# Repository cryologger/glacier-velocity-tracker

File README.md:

# Cryologger - Glacier Velocity Tracker (GVT)
### Note: This documentation is currently under development.

## 1.0 Introduction

Reliance on expensive and proprietary commercial data acquisition and telemetry systems can present a barrier to monitoring remote polar environments. The development of low-cost, open-source instrumentation can greatly reduce the cost of research in remote locations, improve the spatiotemporal resolution of collected data, and provide new ways to observe and monitor the cryosphere. 

The [Cryologger Glacier Velocity Tracker (GVT)](https://github.com/cryologger/glacier-velocity-tracker) is a novel [Cryologger](https://github.com/cryologger) design configuration intended to collect high temporal resolution velocity measurements to assess glacier dynamics on daily timescales in the Canadian Arctic. The system is based on the Arduino electronics platform and harnesses the u-blox ZED-F9P multi-frequency Global Navigation Satellite System (GNSS) receiver.

## 2.0 Methods

### 2.1 Design
The Cryologger GVT is based on the open-source Arduino platform (www.arduino.cc). Code is written using the Arduino Integrated Development Environment (IDE) and benefits from the availability of community-generated libraries.

The design of the Cryologger GVT takes into consideration several key principles, including cost-effectiveness, power efficiency, modularity, ruggedness, and ease of use. It is comprised of off-the-shelf components that do not require specialized tools or training, making it accessible to researchers, citizen scientists, and hobbyists alike. These selected components are also resistant to harsh environmental conditions, ensuring year-round continuous cold-weather operation.

#### 2.1.1 Bill of materials

The Cryologger GVT is built using almost exclusively using components from [SparkFun](https://www.sparkfun.com/), with a list of the main components shown below. For a more detailed bill of materials, including requirements for power and mounting of a complete deployable system, please see [ASSEMBLY.md](/Documentation/ASSEMBLY.md).

**Table 1.** Main components making up Cryologger GVT. Prices are listed in USD and are current as of December 2023. Taxes and shipping are not included.
| Component | Product | Quantity | Cost (USD) |
| --- | --- | :---: | :---: |
| PCB | [Custom Cryologger Printed Circuit Board](https://jlcpcb.com) | 1 | $5.00 | 
| Processor | [SparkFun MicroMod Artemis Processor](https://www.sparkfun.com/products/16401) | 1 | $14.95 | 
| Carrier Board | [SparkFun MicroMod Data Logging Carrier Board](https://www.sparkfun.com/products/16829) | 1 | $21.50 | 
| GNSS Receiver | [SparkFun GPS-RTK-SMA Breakout - ZED-F9P](https://www.sparkfun.com/products/16481) | 1 | $274.95 | 
| GNSS Antenna | [SparkFun GNSS Multi-Band L1/L2 Surveying Antenna (TNC) - TOP106](https://www.sparkfun.com/products/17751) | 1 | $133.95 | 
| Display | [SparkFun Qwiic OLED Display](https://www.sparkfun.com/products/17153) | 1 | $10.95 |
| Voltage Regulator | [Pololu 5V, 600mA Step-Down Voltage Regulator D36V6F5](https://www.pololu.com/product/3792) | 1 | $6.95 |

#### 2.1.2 Design Evolution 

A carrier board was designed to simplify assembly and deployment. It provides 5.08 mm, 2-pin screw terminals for wiring the battery connection, and a resistor divider to measure battery voltage.

<p align="center"><b>Figure 1.</b> Open-source carrier board design.</p>

#### 2.1.3 Mock-up
The Cryologger GVT was originally intended to be installed in a small electronics enclosure that is mounted in a larger enclosure for deployment outdoors.

<p align="center"><b>Figure 2.</b> Open-source carrier board design.</p>

### 2.2 Operation

When initially powered on, the Cryologger GVT will attempt to establish a GNSS fix and synchronize the real-time clock (RTC) of the MicroMod Artemis Processor for up to 5 minutes. Once the RTC is synchronized, the system will set an alarm to wake at the user-specified time and then enter a low-power deep sleep.  Nominally, the system will wake daily and log data from the u-blox GNSS receiver to a microSD card for a period of 3 hours. There are three different logging modes available to the end end-user, which can be tailored to the data collection requirements and available power capacity.

Versions 2.2.1 and above of the Cryologger GVT are equipped with an OLED display. This display is used to provide detailed information to the end user about the status of the Cryologger at each stage of operation, including boot-up, initialization of components, acquisition of GNSS fix, and logging of data. 

In addition to the OLED display messages, a series of LED blink patterns can also be used to indicate system operation and guide possible troubleshooting steps that should be attempted if any errors is encountered. A detailed table of the LED blink patterns can be found in the [DEPLOYMENT.md](/Documentation/DEPLOYMET.md) documentation. 

While the system is in deep sleep, a Watchdog Timer (WDT) will wake the system to check the program has not frozen every 10 seconds and perform a reset, if necessary. This helps to ensure the long-term reliability of the system.

### 2.3 Data Processing

Data is logged in u-blox's proprietary .ubx format. Log files can be converted to RINEX using RTKLIB or Emlid Studio and submitted to NRCan's Precise Point Positioning (PPP) tool: https://webapp.geod.nrcan.gc.ca/geod/tools-outils/ppp.php

For a more detailed guide on the processing of data, please see "[PROCESSING.md](/Documentation/PROCESSING.md).

## 3.0 Deployments

Between 2021 and 2023, a total of 28 Cryologger GVT deployments were made by several different academic institutions, including the Univerity of Ottawa, Carleton University, University of Waterloo (Canada), Carnegie Mellon University (United States), and University of Fribourg (Switzerland). These deployments were made on glaciers in several geographically distinct locations, including Canada, the United States and Kyrgyzstan. Two case studies of deployments made by the University of Ottawa and the University of Waterloo on glaciers in the Yukon and Nunvaut, Canada are explored in more detail below.

<p align="left"><b>Figure 3.</b> Map of Cryologger GVT deployments made between 2021 and 2023.</p>

### 3.1 Lowell Glacier, Yukon, Canada

<p align="left"><b>Figure 4.</b> Map of Cryologger GVT deployments made in 2021 on the Lowell Glacier, Yukon.</p>

### 3.2 Belcher Glacier, Devon Island, Nunavut, Canada

<p align="left"><b>Figure 5.</b> Map of Cryologger GVT deployments made in 2021 on the Lowell Glacier, Yukon and Belcher Glacier, Devon Island, Nunavut.</p>

<p align="center">&nbsp;&nbsp;</p>
<p align="left"><b>Figure 6.</b> Deployment of the "Belcher Lower" Cryologger GVT on the Belcher Glacier, Devon Island, Nunavut.</p>

## 4.0 Results

Preliminary results from the 2021 deployments of Cryologger GVTs on Lowell Glacier, Kluane National Park, Yukon and Belcher Glacier, Devon Island, Nunavut are presented below.

### 4.1 Lowell Glacier, Yukon, Canada

The initial Cryologger GVTs deployments on Lowell Glacier were both successful, achieving continuous operation throughout the year. 

Collected data that was PPP-processed revealed the GVTs deployed on Lowell Glacier were able to achieve daily position measurements with accuracies of <3 cm. Daily displacements ranged between 0.25 – 4.4 m d<sup>-1</sup> and annual cumulative distances were between 200 – 700 m y<sup>-1</sup>. Both systems showed evidence of ongoing glacier surge cycles and excitingly were also able to capture periods of marked glacier velocity corresponding to local rainfall events and enhanced basal sliding.

<p align="left"><b>Figure 7.</b> Cumulative distance and daily displacement of Lowell Glacier, Yukon recorded between between 2021 and 2022.</p>

### 4.2 Belcher Glacier, Devon Island, Nunavut, Canada

Cryologger GVT deployments made on Belcher Glacier were also able to achieve successful operation throughout the entire year. The data collected between 2021-2022 represents the first uninterrupted annual velocity record of the Belcher Glacier ever recorded.

PPP-processed data showed the GVTs deployed on Belcher Glacier were also able to achieve daily position measurements with accuracies of <3 cm. Daily displacements ranged between 0.18 – 0.45 m d<sup>-1</sup> and annual cumulative distances were between 75 – 150 m y<sup>-1</sup>. These results are also in agreement with velocities derived from synthetic-aperture radar (SAR) remote sensing data.

<p align="left"><b>Figure 8.</b> Cumulative distance and daily displacement of Belcher Glacier, Devon Island recorded between between 2021 and 2022.</p>

## 5.0 Conclusions

Cryologger GVT deployments have demonstrated they can achieve continuous year-round operation. Data processed with Precise Point Positioning techniques also reveals the systems can achieve daily position measurements with accuracies of <3 cm. These promising results demonstrate that open-source hardware and software can provide a reliable and cost-effective alternative to commercially available equipment for use in glaciological monitoring.

## Acknowledgements

This project would not have been possible without the designs, software and tutorials provided by the open-source community. A special thanks to the authors of and contributors to the [SparkFun u-blox GNSS Arduino Library](https://github.com/sparkfun/SparkFun_u-blox_GNSS_Arduino_Library).

## Repository Contents

* **/Documentation** - Assembly, deployment and troubleshooting guides, as well as information on components used and associated costs.

* **/Hardware** - KiCad PCB schematic and design files.

* **/Software** -  Arduino code and Python data analysis scripts.

## License Information
Cryologger code, firmware, and software is licensed under the GNU General Public License v3.0 (https://www.gnu.org/licenses/gpl-3.0.en.html). 

<p xmlns:cc="http://creativecommons.org/ns#" >Cryologger hardware is licensed under <a href="https://creativecommons.org/licenses/by-nc-sa/4.0/?ref=chooser-v1" target="_blank" rel="license noopener noreferrer" style="display:inline-block;">CC BY-NC-SA 4.0 </a></p>

Cheers,

**Adam Garbo**

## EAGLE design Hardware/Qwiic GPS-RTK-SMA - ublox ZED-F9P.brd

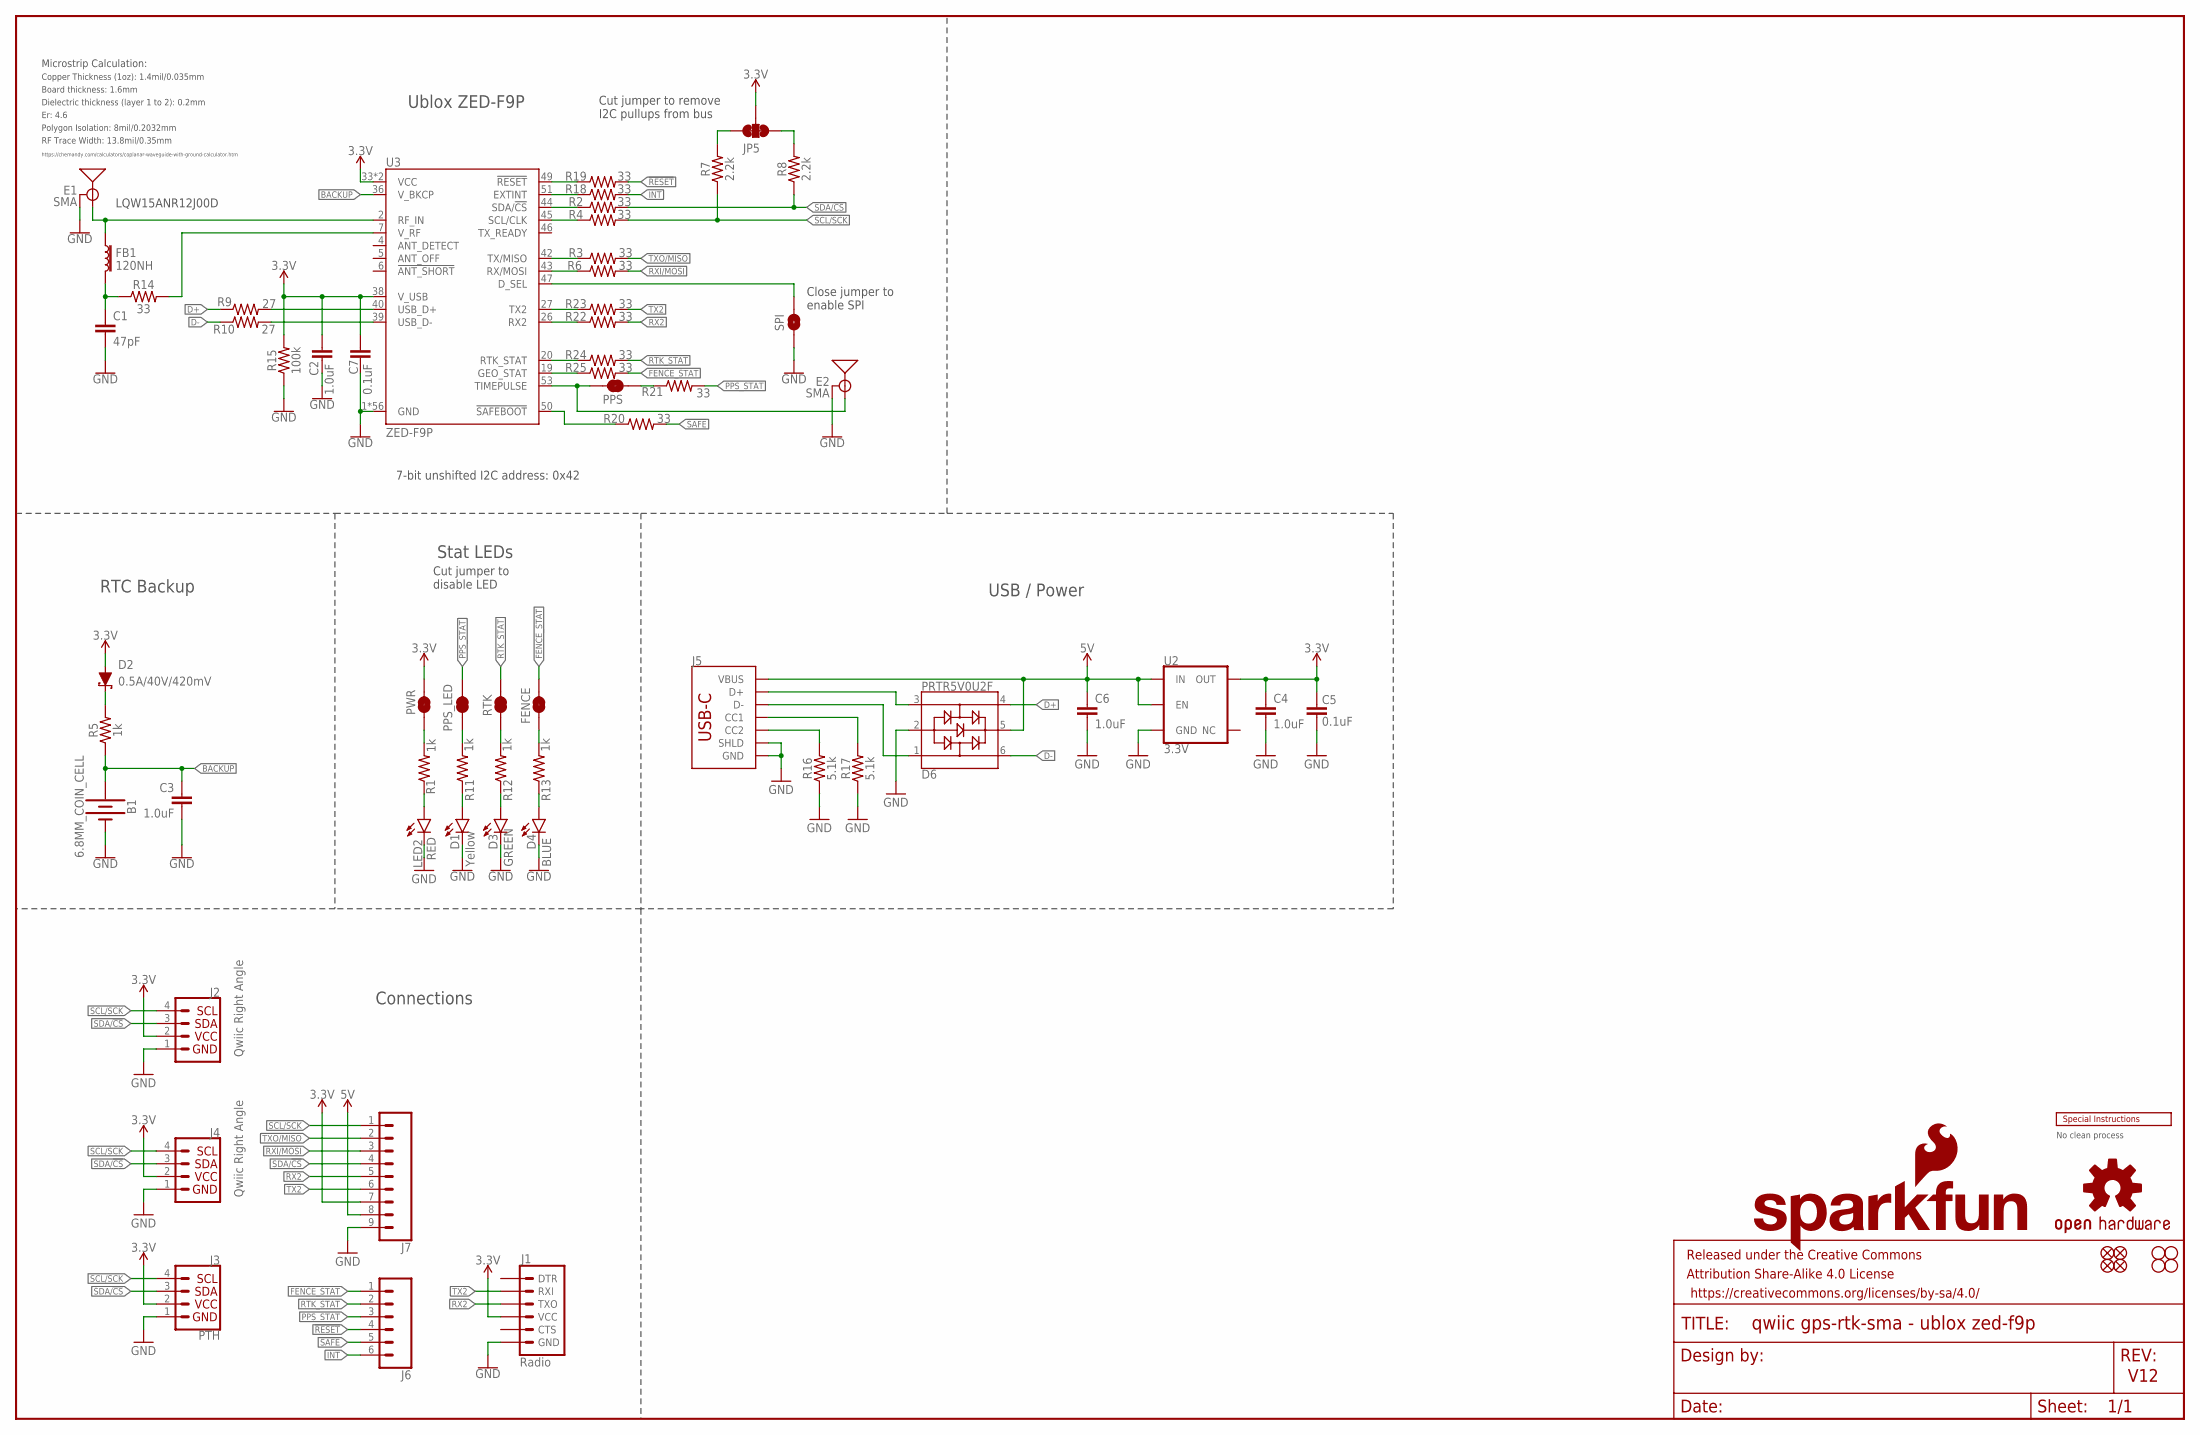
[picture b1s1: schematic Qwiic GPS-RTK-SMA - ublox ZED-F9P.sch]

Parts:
B1: 6.8MM_COIN_CELL; ML414H_IV01E
C1: 47pF; 0402
C2, C3, C4, C6: 1.0uF; 0603
C5, C7: 0.1uF; 0603
D1: Yellow; LED-0603
D2: 0.5A/40V/420mV; SOD-323
D3: GREEN; LED-0603
D4: BLUE; LED-0603
D6: PRTR5V0U2F; SOT886
E1, E2: SMA; SMA-EDGE
FB1: 120NH; 0402_MURATA
FENCE: JUMPER-SMT_2_NC_TRACE_SILK; SMT-JUMPER_2_NC_TRACE_SILK
FRAME2: FRAME-LEDGER; CREATIVE_COMMONS
J1: Radio; 1X06_NO_SILK
J2, J4: Qwiic Right Angle; JST04_1MM_RA
J3: PTH; 1X04_NO_SILK
J5: USB_C_2-LAYER_PADS; USB-C-16P-2LAYER-PADS
J6: CONN_06NO_SILK_FEMALE_PTH; 1X06_NO_SILK
J7: CONN_09NO_SILK; 1X09_NO_SILK
JP5: JUMPER-SMT_3_2-NC_TRACE_SILK; SMT-JUMPER_3_2-NC_TRACE_SILK
JP21, JP61, JP71, JP81: FIDUCIALUFIDUCIAL; MICRO-FIDUCIAL
JP31, JP41, JP91, JP101: STAND-OFF
LED2: RED; LED-0603
LOGO1: OSHW-LOGOMINI; OSHW-LOGO-MINI
LOGO2: SFE_LOGO_NAME_FLAME.1_INCH; SFE_LOGO_NAME_FLAME_.1
PPS: JUMPER-SMT_2_NC_TRACE_SILK; SMT-JUMPER_2_NC_TRACE_SILK
PPS_LED: JUMPER-SMT_2_NC_TRACE_SILK; SMT-JUMPER_2_NC_TRACE_SILK
PWR: JUMPER-SMT_2_NC_TRACE_SILK; SMT-JUMPER_2_NC_TRACE_SILK
R1, R5, R11, R12, R13: 1k; 0603
R2, R3, R4, R6, R14, R18, R19, R20, R21, R22, R23, R24, R25: 33; 0603
R7, R8: 2.2k; 0603
R9, R10: 27; 0603
R15: 100k; 0603
R16, R17: 5.1k; 0603
RTK: JUMPER-SMT_2_NC_TRACE_SILK; SMT-JUMPER_2_NC_TRACE_SILK
SPI: JUMPER-SMT_2_NO_SILK; SMT-JUMPER_2_NO_SILK
U2: 3.3V; SOT23-5
U3: ZED-F9P
U$2: SPECIAL_INSTRUCTIONS-ORDERING; ORDERING_INSTRUCTIONS

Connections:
3.3V: C2.1, C4.1, C5.2, C7.2, D2.A, J1.4 (VCC), J2.2, J3.2 (VCC), J4.2, J7.7, JP5.2, PWR.2, R15.2, U2.5 (OUT), U3.33 (VCC), U3.34 (VCC), U3.38 (V_USB)
5V: C6.1, D6.5, J5.VBUS1 (VBUS), J5.VBUS2 (VBUS), J7.8, U2.1 (IN), U2.3 (EN)
!RESET: J6.4, R19.2
!SAFE: J6.5, R20.2
ANT_VCC: C1.1, FB1.P2 (2), R14.1
BACKUP: B1.+, C3.1, R5.1, U3.36 (V_BKCP)
CC1: J5.A5 (CC1), R17.2
CC2: J5.B5 (CC2), R16.2
D+: D6.4, R9.1
D-: D6.6, R10.1
D_SEL: SPI.2, U3.47 (D_SEL)
FENCE_STAT: FENCE.2, J6.1, R25.2
GND: B1.-, C1.2, C2.2, C3.2, C4.2, C5.1, C6.2, C7.1, D1.C, D3.C, D4.C, D6.2, E1.GND@0 (GND), E1.GND@1 (GND), E1.GND@2 (GND), E1.GND@3 (GND), E2.GND@0 (GND), E2.GND@1 (GND), E2.GND@2 (GND), E2.GND@3 (GND), J1.6 (GND), J2.1, J3.1 (GND), J4.1, J5.GND, J5.GND2 (GND), J5.SHLD1 (SHLD), J5.SHLD2 (SHLD), J5.SHLD3 (SHLD), J5.SHLD4 (SHLD), J7.9, LED2.C, R15.1, R16.1, R17.1, SPI.1, U2.2 (GND), U3.1 (GND), U3.3 (GND), U3.12 (GND), U3.14 (GND), U3.32 (GND), U3.37 (GND), U3.41 (GND), U3.48 (GND), U3.55 (GND), U3.56 (GND), U3.57 (GND), U3.58 (GND), U3.59 (GND), U3.60 (GND), U3.61 (GND), U3.62 (GND), U3.63 (GND), U3.64 (GND), U3.65 (GND), U3.66 (GND), U3.67 (GND), U3.68 (GND), U3.69 (GND), U3.70 (GND), U3.71 (GND), U3.72 (GND), U3.73 (GND), U3.74 (GND), U3.75 (GND), U3.76 (GND), U3.77 (GND), U3.78 (GND), U3.79 (GND), U3.80 (GND), U3.81 (GND), U3.82 (GND), U3.83 (GND), U3.84 (GND), U3.85 (GND), U3.86 (GND), U3.87 (GND), U3.88 (GND), U3.89 (GND), U3.90 (GND), U3.91 (GND), U3.92 (GND), U3.93 (GND), U3.94 (GND), U3.95 (GND), U3.96 (GND), U3.97 (GND), U3.98 (GND), U3.99 (GND), U3.100 (GND), U3.101 (GND), U3.102 (GND)
GPS_ANT1: E1.SIG (SIGNAL), FB1.P1 (1), U3.2 (RF_IN)
INT: J6.6, R18.2
unnamed: D3.A, R12.1
unnamed: D1.A, R11.1
unnamed: R12.2, RTK.1
unnamed: PPS_LED.1, R11.2
unnamed: JP5.1, R8.2
unnamed: D2.C, R5.2
unnamed: D4.A, R13.1
unnamed: JP5.3, R7.2
unnamed: FENCE.1, R13.2
unnamed: LED2.A, R1.1
unnamed: R9.2, U3.40 (USB_D+)
unnamed: R10.2, U3.39 (USB_D-)
unnamed: R14.2, U3.7 (V_RF)
unnamed: R22.1, U3.26 (RX2)
unnamed: R18.1, U3.51 (EXTINT)
unnamed: R19.1, U3.49 (!RESET!)
unnamed: PWR.1, R1.2
unnamed: R20.1, U3.50 (!SAFEBOOT!)
unnamed: R24.1, U3.20 (RTK_STAT)
unnamed: R25.1, U3.19 (GEO_STAT)
unnamed: PPS.1, R21.1
PPS: E2.SIG (SIGNAL), PPS.2, U3.53 (TIMEPULSE)
PPS_STAT: J6.3, PPS_LED.2, R21.2
RTK_STAT: J6.2, R24.2, RTK.2
RX2: J1.3 (TXO), J7.5, R22.2
RXI/MOSI: J7.3, R6.2
RXLV: R6.1, U3.43 (RX/MOSI)
SCL/SCK: J2.4, J3.4 (SCL), J4.4, J7.1, R4.2, R7.1
SCL_LV: R4.1, U3.45 (SCL/CLK)
SDA/!CS: J2.3, J3.3 (SDA), J4.3, J7.4, R2.2, R8.1
SDA_LV: R2.1, U3.44 (SDA/!CS!)
TX2: J1.2 (RXI), J7.6, R23.2
TX2_P: R23.1, U3.27 (TX2)
TXLV: R3.1, U3.42 (TX/MISO)
TXO/MISO: J7.2, R3.2
UNP_D+: D6.3, J5.A6 (D+), J5.B6 (D+)
UNP_D-: D6.1, J5.A7 (D-), J5.B7 (D-)

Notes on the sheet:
V12
7-bit unshifted I2C address: 0x42
Ublox ZED-F9P
RTC Backup
Stat LEDs
Cut jumper to remove I2C pullups from bus
Cut jumper to disable LED
Close jumper to enable SPI
LQW15ANR12J00D
Board thickness: 1.6mm
Er: 4.6
Copper Thickness (1oz): 1.4mil/0.035mm
RF Trace Width: 13.8mil/0.35mm
Polygon Isolation: 8mil/0.2032mm
No clean process
Dielectric thickness (layer 1 to 2): 0.2mm
https://chemandy.com/calculators/coplanar-waveguide-with-ground-calculator.htm
Microstrip Calculation:
Connections
USB / Power

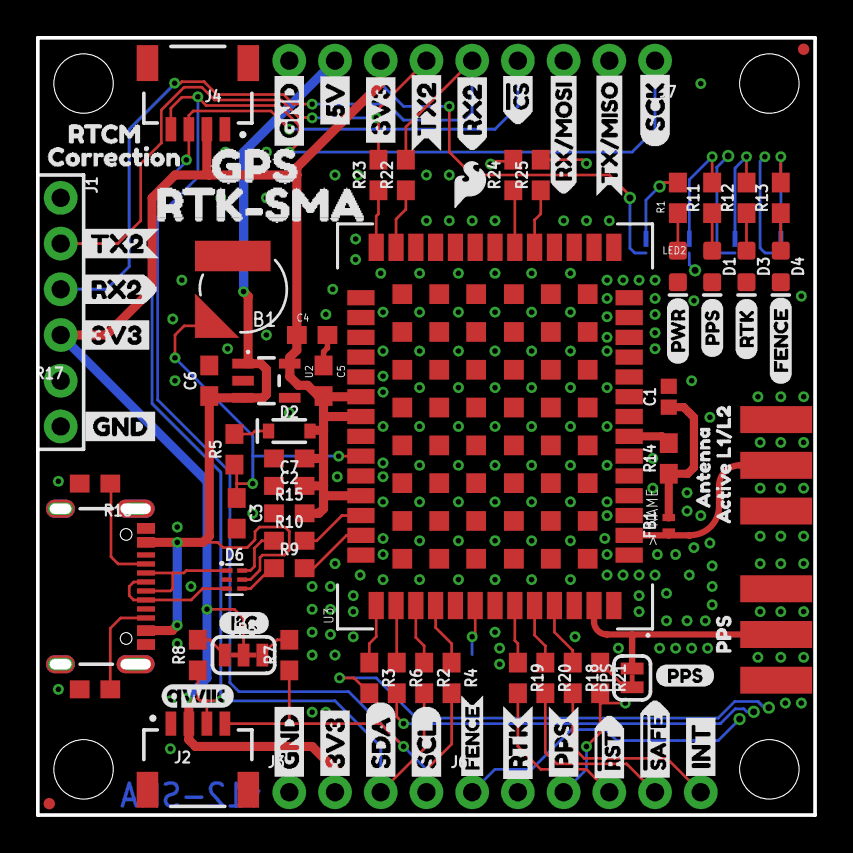
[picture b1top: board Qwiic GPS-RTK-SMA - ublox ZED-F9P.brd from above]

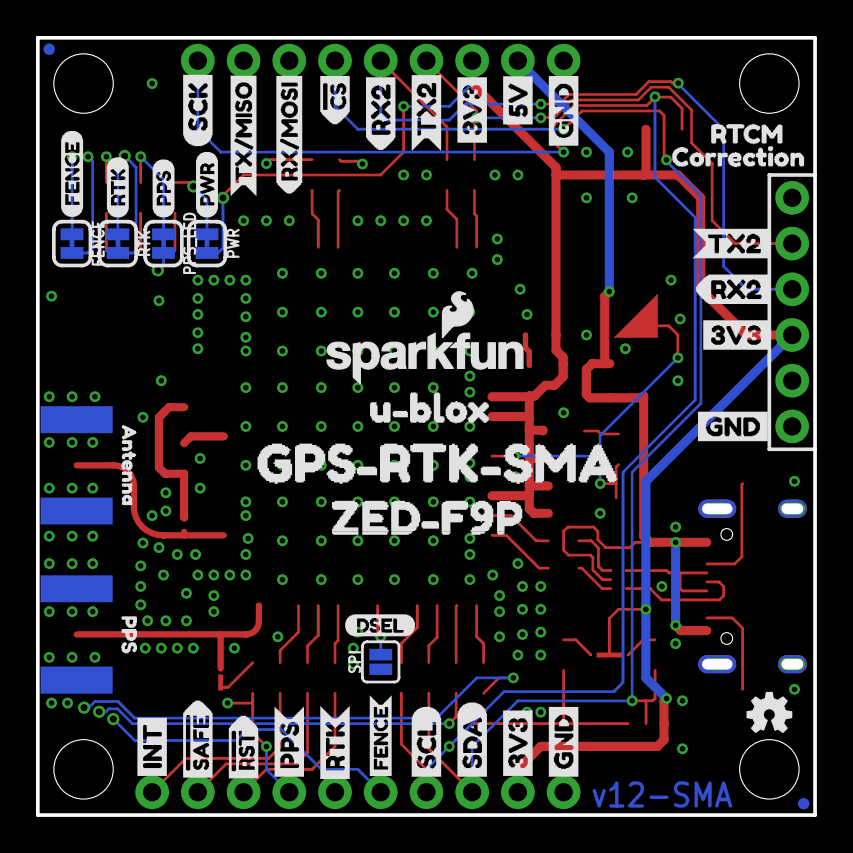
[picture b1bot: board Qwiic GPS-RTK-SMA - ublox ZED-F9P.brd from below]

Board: 4 copper layers, 43.2 x 43.2 mm, 143 parts (44 on the bottom side), 52 nets.

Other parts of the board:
U$1, U$4: SDA-[)
U$3, U$5: SCL-[)
U$6, U$7, U$60, U$61, U$66, U$67: 3V3-04
U$8, U$9, U$62, U$63: GND-04
U$10: I_SUPER2_C-()-03
U$11, U$54: FENCE2
U$12, U$18: PWR-()-03
U$13, U$28, U$29, U$32: RTK1
U$14, U$17: FENCE0
U$15, U$16: INT8
U$19, U$20: 5V
U$21, U$56, U$58: RX20
U$22: U#BLOX3
U$23, U$24: CS#-<]
U$25, U$52, U$72: PPS0
U$26, U$31: RX#MOSI3
U$27: DSEL0
U$30: QWIIC_4MM
U$33: SFE_LOGO_FLAME_.1
U$34, U$37: TX#MISO1
U$35, U$36: #RST3
U$38, U$41: SCK-(]-04
U$39, U$40: #SAFE1
U$42: RX22
U$43, U$44: PPS5
U$45, U$68: GND3
U$47, U$74: PPS1
U$48, U$70: RTCM5
U$49: ZED#F9P6
U$50, U$55, U$57: TX21
U$51: TX23
U$53, U$69: CORRECTION0
U$59: GPS0
U$65: ACTIVE_L1#L21
U$71, U$75: ANTENNA2
U$73: RTK#SMA4
U$76: GPS#RTK#SMA5

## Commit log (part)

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2021-03-23 Remove Apollo3 Core v2.x modifications
2021-03-23 Update testing results
2021-03-24 Begin to add OLED code
2021-03-24 Add sleep option
2021-03-24 Modify low-power code
2021-03-25 Add debugging and disableUBX7Fcheck() functions
2021-03-26 Add specific alarm timings
2021-03-27 Add RTC drift calculation
2021-03-30 Add u-blox epoch time functionality
2021-03-30 Change RTC sync code to use getPVT instead of callbacks
2021-03-31 Remove OLED functionality
2021-04-01 Convert print statements to debug macros
2021-04-02 Consolidate MicroMod code versions
2021-04-02 Move log file name timestamping to separate function
2021-04-03 Add logging settings print function
2021-04-03 Add initialization failure reattempt code
2021-04-03 Remove OLA code
2021-04-03 Add logging mode, prepare for initial release
2021-04-04 Add additional debugging variables
2021-04-05 Disable Artemis internal pull-ups
2021-04-05 Begin to add conditional code for initialization failures
2021-04-06 Update version
2021-04-11 Rename software
2021-04-13 Minor update
2021-04-14 Add KiCad project files
2021-04-28 Troubleshooting u-blox initialization failures
2021-04-28 Fix u-blox power source functionality
2021-05-25 Re-enable control over Qwiic power
2021-06-22 Update KiCad files
2021-07-04 Improve blink pattern indicators
2021-07-04 Preparation of deployment code
2021-07-10 Fix GitHub library URL
2021-07-22 Add unique identifier to log and debug files
2021-12-08 Rename repository files
2022-03-13 Add updated KiCad files
2022-03-24 Add functionality to read battery voltage
    Configure system for testing prior to deployment
2022-03-27 Add support for OLED display
    Improve automatic logfile timestamp naming function
2022-03-27 Add 24-hour logging mode
    Minor WDT code comment improvements. Change read voltage function to return values. Add function to get time and print to buffer.
2022-03-29 Improve OLED code
    Add explicit control over internal pull-up resistors. Incorporate new reset function allowing OLED to recover from sleep/power cycles.
2022-03-29 Upload Gerber files
2022-03-29 Rename Gerber files
2022-03-30 Change delays to blocking for WDT reset
    Power down Qwiic connector and microSD when forcing a WDT reset.
2022-03-31 Move disabling pull-ups to before Wire.end()
    Make battery voltage analog reading global.
2022-03-31 Adjust delays
2022-03-31 Improve code commenting
2022-03-31 Remove setting of alarm flag causing false triggers
2022-04-04 Adjust gain and offset
    Values based on more in-depth characterization of resistor divider cirucit.
2022-04-04 Put OLED display to sleep after number of cycles
    Clean up RTC code. Add delay after RTC sync in order to be able to view drift value.
2022-04-04 Create LICENSE
2022-04-14 Update bill of materials
2022-04-24 Minor updates
2022-04-28 Added scheduled deep sleep mode
    Decreased WDT frequency.
2022-06-21 Remove scheduled sleep functionality
    Prepare code for future deployments on Ellesmere Island.
2022-06-21 Minor updates
    Improve log file naming. Rename tabs to standardized Cryologger names (i.e., logging, debug). Improve debug print statements.
2022-06-21 Adjust version number
2022-06-21 Adjust OLED display selection
2022-06-25 Hard code logging and sleep alarm modes based on operation
2022-06-25 Rename column header
2022-06-25 Add toggle code for OLED to prevent hanging
2022-06-25 Updates for deployment testing
2022-06-27 Update OLED display version
2022-06-27 Configure for continuous logging as default
2022-08-02 Improve OLED display messages
2022-08-03 Add missing constellation configuration options
2022-08-03 Rearrange order of microSD initialization
2022-08-04 Minor improvements to OLED display messages
2022-08-04 Minor updates
    Improved code commenting. Removal of LED blink patterns.
2022-08-04 Minor updates
    Improve unique identifier to include 3-letter abbreviation and unit number. Add additional OLED display messages.
2022-08-04 Update library versions
2022-08-15 Add PCB design revision v2.2
    Organize existing KiCad hardware and Gerber files. Create new global library symbols and footprints.
2022-08-23 Add OLED display reinitialization functionality
2022-08-23 Fix orientation of PCB OLED mounting holes
2022-08-23 Minor updates
    Prepare code for 2022 Lowell Glacier deployments. Create 3D PCB image.
2022-09-01 OLED display message improvements
2022-09-01 Revert "Update version"
    This reverts commit ccc04b14ab65624194f0727ee538848e1a4a9334.
2022-09-01 Update logging start and stop times for deployment
2022-12-05 Enable Galileo constellation
2023-03-17 Rename folders
    Removed old KiCad files.
2023-03-19 Organize folders
2023-03-28 Migrate code to SparkFun u-blox GNSS v3 library
2023-03-28 Update library version
2023-04-02 Migrate code to v3 method of querying u-blox registers
2023-04-02 Migrate code to SparkFun u-blox GNSS v3 library
    Standardized debug print statements. Removed code that would cause system to enter reset loop if component failure was encountered.
2023-04-02 Correct debug typos
2023-04-02 Configure code for testing
2023-04-08 Add 3D-printed solar panel drill guide files
2023-04-08 Add enclosure drill pattern files
2023-04-09 Adopt naming convention to make variable names more standardized/generic
2023-04-15 Add 3D-printing drill guide files
2023-04-28 Minor updates for v2.2 release
2023-04-29 Move documentation files
2023-04-29 Remove v1.0 archived files
2023-04-29 Organize and remove old KiCad files
2023-04-29 Configured for Arctic Bay deployments
2023-04-29 Update version number
2023-06-19 Add images for assembly documentation
2023-06-23 Set alarm modes from within alarm functions
    Added alarm hour and minute for daily logging mode. Updated corresponding debugging and display code.
2023-06-26 Major alarm improvements
    Integrated alarm modes directly into logging and sleep functions. Added minutes functionality to daily alarms. Updated relevant display and debugging code. Removed unnecessary return; commands.
2023-06-26 Minor GNSS updates
    Reverted GNSS timeout to seconds. Moved functions to appropriate tabs.
2023-06-26 Update cryologger_gvt.ino
    Updated variable names to consistent style. Improved daily and rolling alarm functionality. Added a daily check to sync RTC. Avoided unnecessary reinitialization of devices when in continuous mode. I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
2023-06-28 Correction to turn OLED display after specified period of time
2023-07-11 Upload documentation images
2023-07-11 Update image filename convention
    Added annotations to screenshots.
2023-07-11 Being updates to revert to Arduino IDE 1.8.x
2023-07-11 Rename file
2023-07-11 Continue revisions to revert to Arduino IDE v1.8.x
2023-07-12 Standardize image filenames
2023-07-12 Update image with identical file name
2023-08-07 Add documentation screenshots
2023-12-05 Remove G-Code
2024-01-12 Minor update to comments
2024-01-17 Include additional license information
2024-01-17 Add DOI badge
2024-03-11 Remove EAGLE files
2024-06-08 Fix typos
2024-09-19 Delete Documentation/SERVICING.md
    To be replaced by site-agnostic documentation.
2025-02-17 Add seasonal logging functionality
    Improved code commenting. Changed alarms to switch case. Adopted Clang 14.0.0 formatting. Added software and hardware versions. Changed unique identifier to serial number.
2025-02-17 Improve code commenting
    Adopted Clang 14.0.0 formatting.
2025-02-17 Improve microSD initialization logic
2025-02-17 Improve log file write and debug print logic
    Adopted serial number for log files.
2025-02-17 Add missing functions
2025-02-17 Improve efficiency of debug printing
2025-02-17 Add missing function
2025-02-17 Add new peripheral power restore function
2025-02-17 Major changes to summer logging mode
    Reworked code to gracefully enter and exit summer logging mode.
2025-02-17 Refinements to summer logging mode
2025-02-18 Apply Clang 14.0.0 formatting
2025-02-18 Refine summer mode logging
    Added debugging code to test all power-on scenarios.
2025-02-18 Improve code commenting
    Set test settings.
2025-02-21 Add check to close open debug file
2025-02-21 Seasonal logging mode improvements
    Changed naming convention to seasonal instead of summer logging mode. Eliminated initial alarm. Changed to day of year (DOY) approach for determining seasonal mode instead of MMDD.
2025-02-23 Improve code commenting
    Added GNSS firmware query to debugging.
2025-02-23 Add configuration from microSD card functionality
    System settings made configurable from JSON config file on microSD card.
2025-02-23 Add new user configuration section
    Improved code commenting. Changes related to new JSON config file located on microSD card.
2025-02-23 Make satellites configurable
    Added new variables to make satellites configurable from user section or JSON config file on microSD card.
2025-02-27 Add functionality to get microSD storage and file count
2025-03-05 Remove F() from Serial print statements
    Changed sprintf() specifiers to match variable types.
2025-03-05 Revert to simplified debug logging
    Removed Serial print statement from sleep function.
2025-03-05 Add GNSS and microSD display functions
2025-03-05 Move JSON config loading to setup
2025-03-06 Improve GNSS-related code
    Enhanced GNSS receiver initialization logic. Added configuration code to functions. Improved code commenting. No functional logging changes.
2025-03-08 Add missing checks for microSD online flag
2025-03-10 Add GNSS measurement rate to configuration file
2025-03-12 Improve JSON config file loading
    Enhanced variable validity checks.
2025-03-15 Add config.json file
2025-03-18 Remove F() from Serial print statements
2025-03-18 Use snprintf instead of sprintf to enforce bounds
    Applied Auto Format in Arduino 2.x to ensure proper formatting.
2025-03-18 Add JSON config OLED display message
    Changed approach for tracking validity of JSON configuration variables.
2025-03-18 Remove ArduinoJSON deprecated containsKey() calls and replace with doc["key"].is<T>()
    Changed displayInitialize() function to use const char *device.
2025-03-18 Add seasonal logging mode display message on OLED
2025-03-20 Address code commenting issues
2025-03-21 Increase RTC sync timeout period
    Decreased number of valid fixes required to sync RTC with GNSS.
2025-03-28 Default RTC sync GNSS measurement rate to 1 Hz
2025-03-28 Returned minimum fix counter to 10
2025-04-24 Update required libraries
2025-04-27 Remove Python files
2025-04-28 Change default measurement rate to 1 Hz
2025-06-12 Add additional OLED display screen
2025-06-12 Update software version
2025-06-13 Add boot display screen
    Adjusted spacing of GNSS info display screen.
2025-06-13 Update date
2025-06-15 Update badges
2025-07-03 Update libraries
2025-07-03 Fix CITATION.cff version to match tag v3.0.3
2025-07-04 Add link to CH340 drivers
2026-02-27 Update OLED display code
    Improved OLED initialization logic when the display was not physically connected but enabled in config. Added I2C device probing and improved pull-up stabilization timing.
2026-04-13 Update DOI badge
2026-04-16 Improve code comments.
2026-04-20 Update BoM
2026-04-26 Update code comments.
2026-04-26 Minor updates
    Improved logic to restore peripherals. Updated library versions. Improved comments.
2026-04-26 Update default config.json
    Disabled seasonal logging mode by default.
2026-04-28 Update bill of material pricing
2026-06-27 Minor OLED fix
2026-06-27 Improve code comments
2026-06-27 Reduce OLED display duration
2026-06-27 Update library versions and improve code comments
2026-06-27 Add functionality to track internal CPU temperature
2026-06-27 Add flag to enable immediate logging on first daily cycle

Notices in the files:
parts and their libraries:
SparkFun-Resistors: Licensing: Creative Commons ShareAlike 4.0 International - https://creativecommons.org/licenses/by-sa/4.0
SparkFun-Aesthetics: Released under the Creative Commons Attribution Share-Alike 4.0 License
SparkFun-Aesthetics: https://creativecommons.org/licenses/by-sa/4.0
